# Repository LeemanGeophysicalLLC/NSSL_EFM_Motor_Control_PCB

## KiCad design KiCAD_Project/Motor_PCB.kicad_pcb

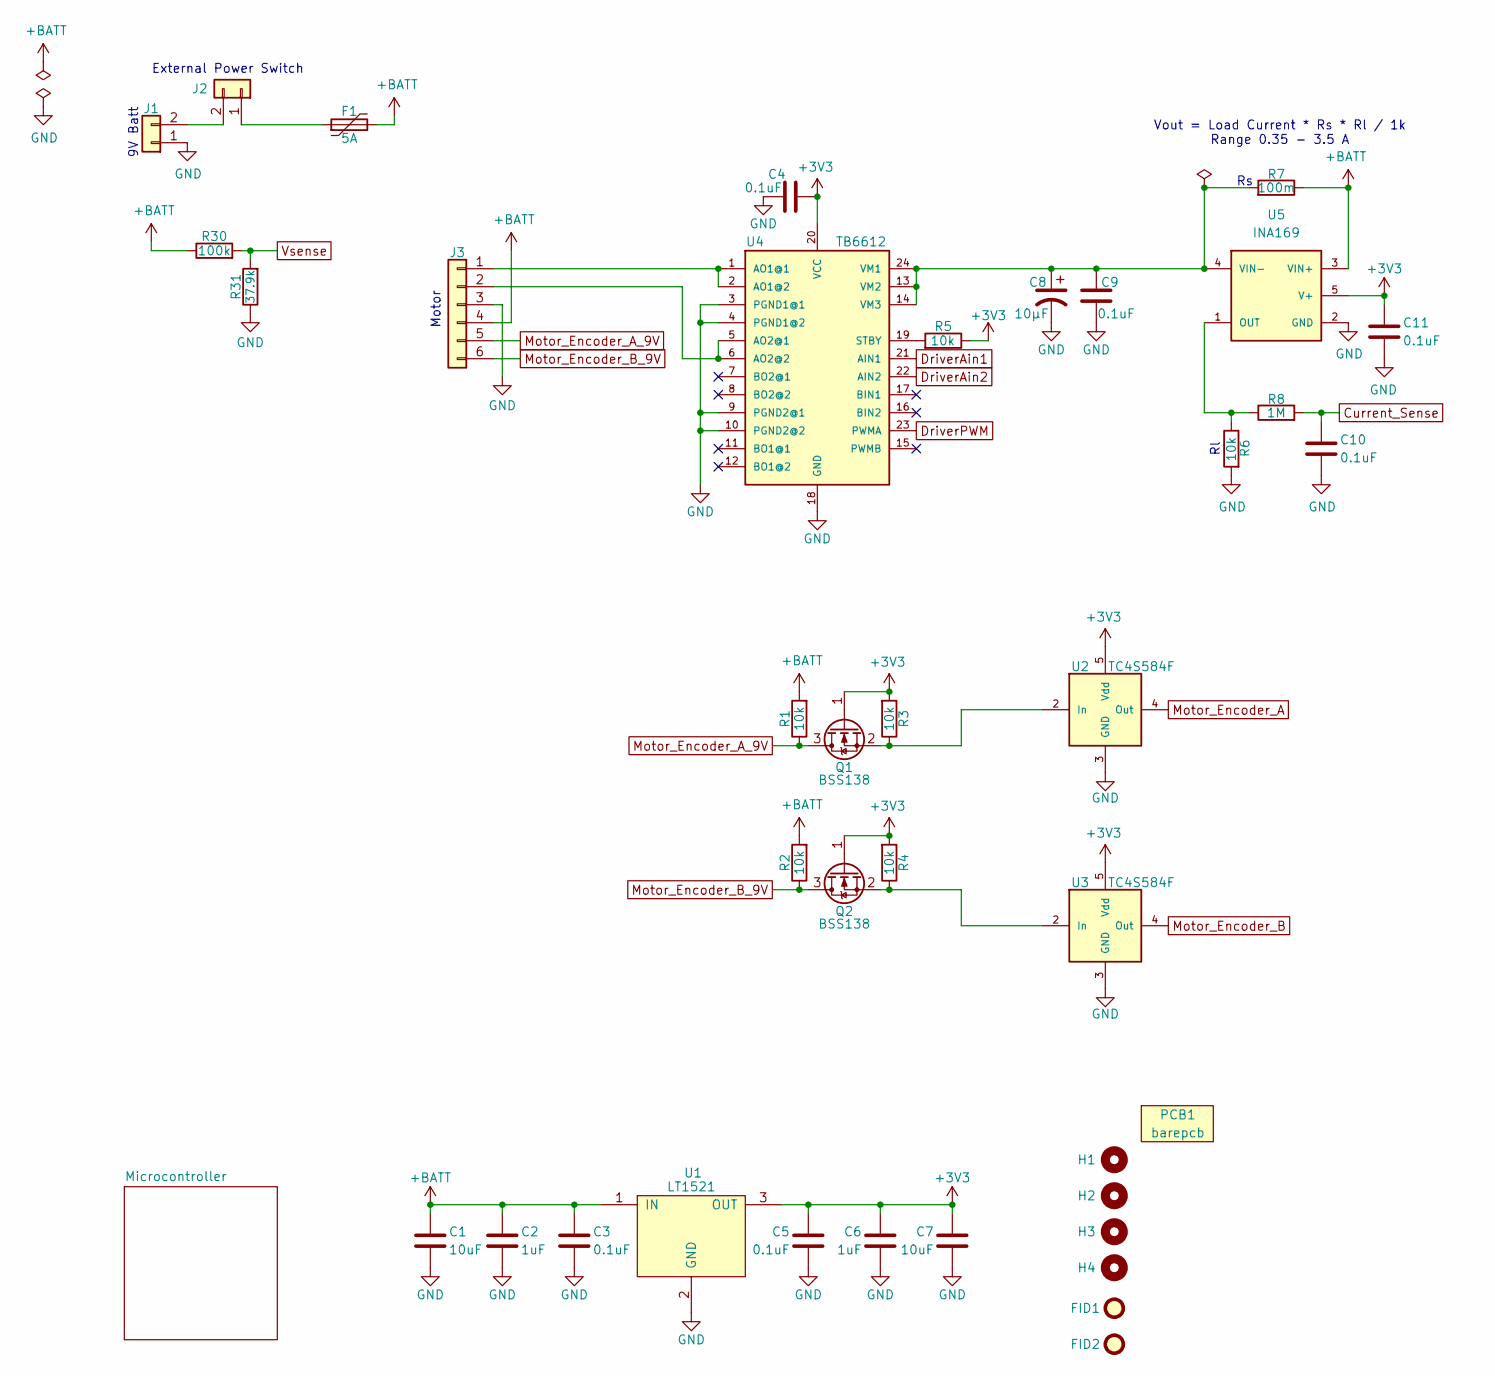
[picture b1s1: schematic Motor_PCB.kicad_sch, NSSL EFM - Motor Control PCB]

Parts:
C1, C7: 1-0000005
C2, C6: 1-0000018
C3, C4, C5, C9, C10, C11: 1-0000007
C8: 1-0000176
F1: 1-0001547
FID1, FID2: Fiducial_1mm_2mm; Fiducial_1mm_Mask2mm
H1, H2, H3, H4: Imperial4; MountingHole_imperial4
J1, J2: NP_Conn_01x02_Relief; SolderWire_1x02_Relief
J3: NP_Conn_01x06; PinHeader_1x06_P2.54mm_Horizontal
PCB1: barepcb
Q1, Q2: 1-0000163
R1, R2, R3, R4, R5, R6: 1-0000010
R7: 1-0001546
R8: 1-0000009
R30: 1-0000174
R31: 1-0001756
U1: 1-0000196
U2, U3: 1-0000456
U4: 1-0001532
U5: 1-0000452

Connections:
+3V3: C4.2, C5.1, C6.1, C7.1, C11.1, Q1.1 (G), Q2.1 (G), R3.2, R4.2, R5.1, U1.3 (OUT), U2.5 (Vdd), U3.5 (Vdd), U4.20 (VCC), U5.5 (V+); also elsewhere on the board
+BATT: C1.1, C2.1, C3.1, F1.2, J3.4, R1.2, R2.2, R7.1, R30.1, U1.1 (IN), U5.3 (VIN+)
Current_Sense: C10.1, R8.2; also elsewhere on the board
DriverAin1: U4.21 (AIN1); also elsewhere on the board
DriverAin2: U4.22 (AIN2); also elsewhere on the board
DriverPWM: U4.23 (PWMA); also elsewhere on the board
GND: C1.2, C2.2, C3.2, C4.1, C5.2, C6.2, C7.2, C8.2, C9.1, C10.2, C11.2, J1.1, J3.3, R6.2, R31.1, U1.2 (GND), U2.3 (GND), U3.3 (GND), U4.3 (PGND1@1), U4.4 (PGND1@2), U4.9 (PGND2@1), U4.10 (PGND2@2), U4.18 (GND), U5.2 (GND); also elsewhere on the board
Motor_Encoder_A: U2.4 (Out); also elsewhere on the board
Motor_Encoder_A_9V: J3.5, Q1.3 (D), R1.1
Motor_Encoder_B: U3.4 (Out); also elsewhere on the board
Motor_Encoder_B_9V: J3.6, Q2.3 (D), R2.1
unnamed: J1.2, J2.2
unnamed: F1.1, J2.1
unnamed: J3.1, U4.1 (AO1@1), U4.2 (AO1@2)
unnamed: J3.2, U4.5 (AO2@1), U4.6 (AO2@2)
unnamed: Q1.2 (S), R3.1, U2.2 (In)
unnamed: Q2.2 (S), R4.1, U3.2 (In)
unnamed: R5.2, U4.19 (STBY)
unnamed: C8.1, C9.2, R7.2, U4.13 (VM2), U4.14 (VM3), U4.24 (VM1), U5.4 (VIN-)
unnamed: R6.1, R8.1, U5.1 (OUT)
Vsense: R30.2, R31.2; also elsewhere on the board

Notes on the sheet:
Motor
External Power Switch
9V Batt
Vout = Load Current * Rs * Rl / 1k Range 0.35 - 3.5 A

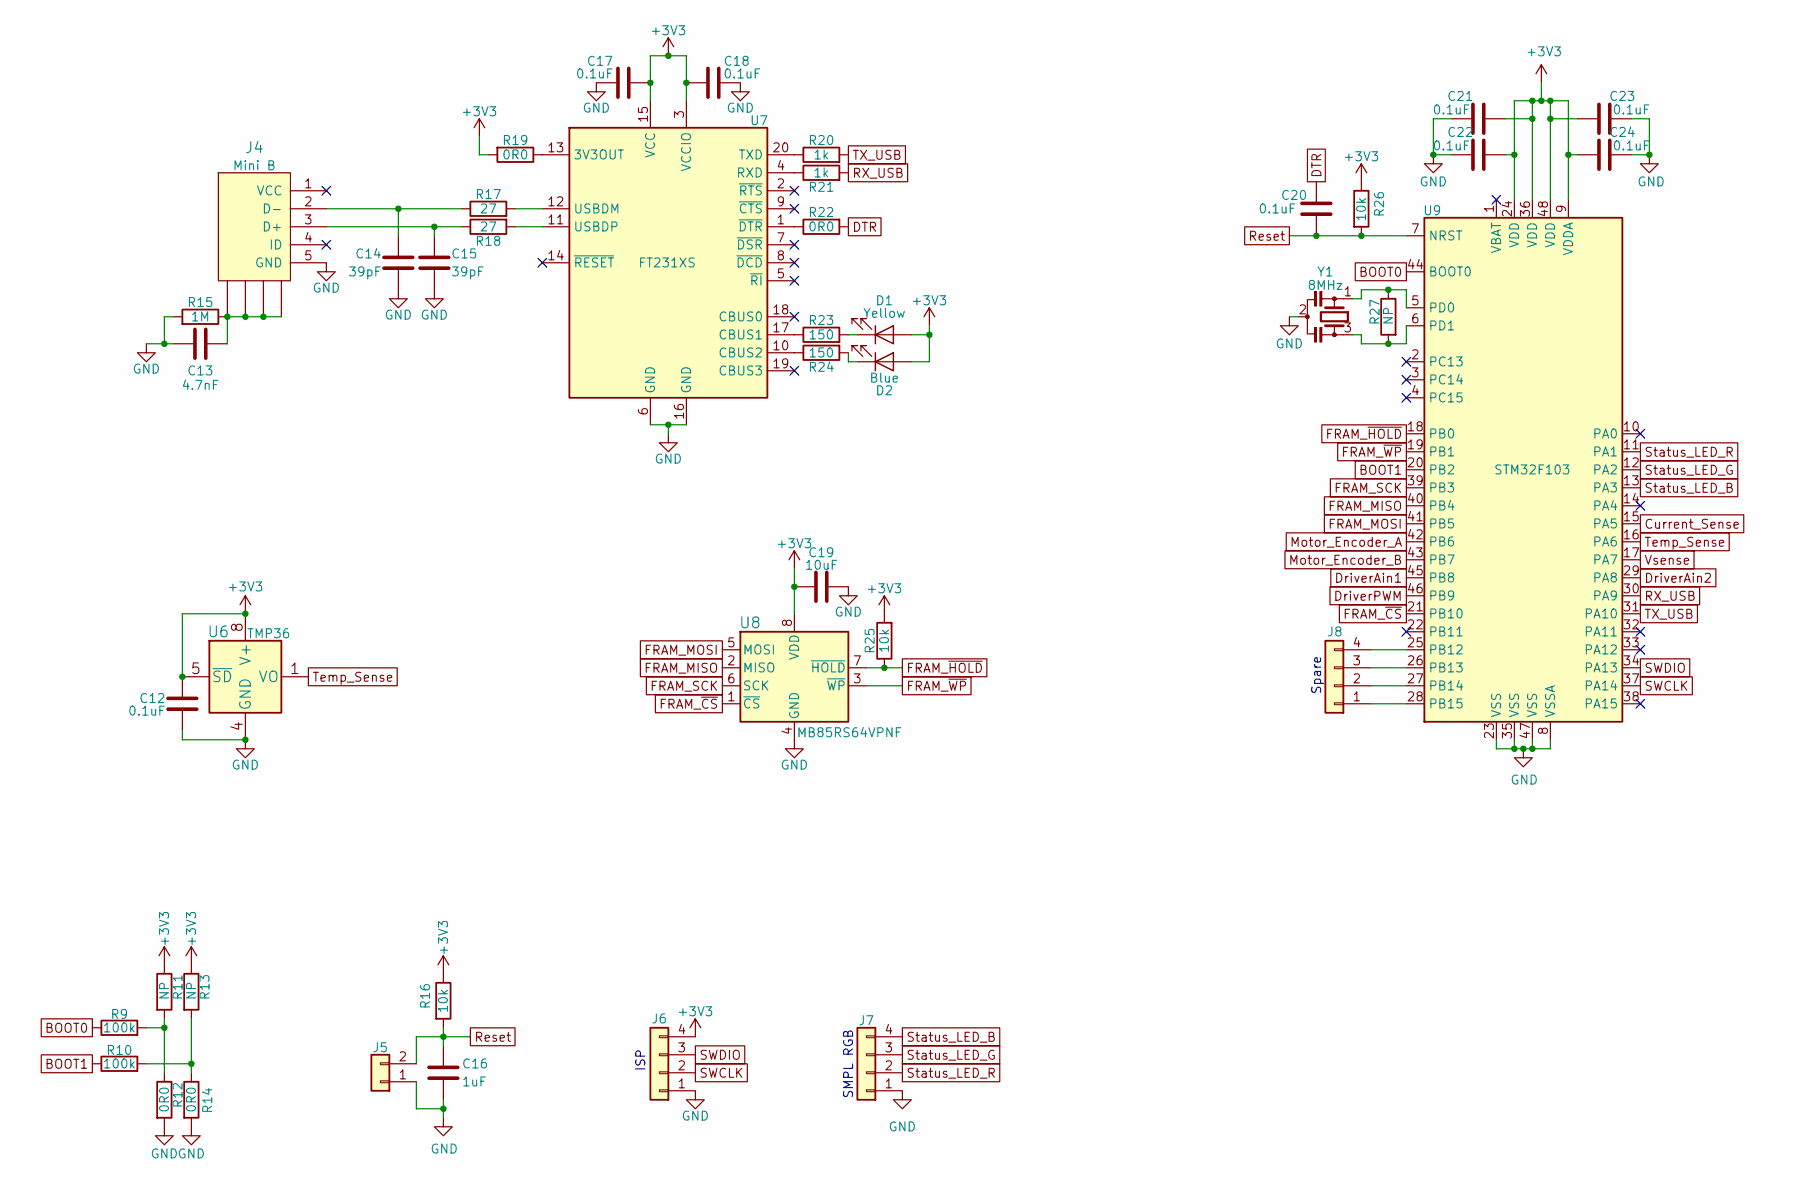
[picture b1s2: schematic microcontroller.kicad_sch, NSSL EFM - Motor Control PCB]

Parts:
C12, C17, C18, C20, C21, C22, C23, C24: 1-0000007
C13: 1-0000016
C14, C15: 1-0000017
C16: 1-0000018
C19: 1-0000005
D1: 1-0000601
D2: 1-0000599
J4: 1-0000034
J5: NP_Conn_01x02; PinHeader_1x02_P2.54mm_Vertical
J6, J8: NP_Conn_01x04; PinHeader_1x04_P2.54mm_Vertical
J7: 1-0001156
R9, R10: 1-0000174
R11, R12, R13, R14, R19, R22, R27: 1-0000006
R15: 1-0000009
R16, R25, R26: 1-0000010
R17, R18: 1-0000012
R20, R21: 1-0000013
R23, R24: 1-0000008
U6: 1-0001493
U7: 1-0000779
U8: 1-0001755
U9: 1-0000207
Y1: 1-0000721

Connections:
+3V3: C12.1, C17.2, C18.2, C19.1, C21.1, C22.1, C23.1, C24.1, D1.2 (A), D2.2 (A), J6.4, R11.1, R13.1, R16.1, R19.2, R25.2, R26.1, U6.5 (~SD), U6.8 (V+), U7.3 (VCCIO), U7.15 (VCC), U8.8 (VDD), U9.9 (VDDA), U9.24 (VDD), U9.36 (VDD), U9.48 (VDD); also elsewhere on the board
BOOT0: R9.1, U9.44 (BOOT0)
BOOT1: R10.1, U9.20 (PB2)
Current_Sense: U9.15 (PA5); also elsewhere on the board
DTR: C20.1, R22.2
DriverAin1: U9.45 (PB8); also elsewhere on the board
DriverAin2: U9.29 (PA8); also elsewhere on the board
DriverPWM: U9.46 (PB9); also elsewhere on the board
FRAM_MISO: U8.2 (MISO), U9.40 (PB4)
FRAM_MOSI: U8.5 (MOSI), U9.41 (PB5)
FRAM_SCK: U8.6 (SCK), U9.39 (PB3)
FRAM_~CS: U8.1 (~CS), U9.21 (PB10)
FRAM_~HOLD: R25.1, U8.7 (~HOLD), U9.18 (PB0)
FRAM_~WP: U8.3 (~WP), U9.19 (PB1)
GND: C12.2, C13.2, C14.2, C15.2, C16.2, C17.1, C18.1, C19.2, C21.2, C22.2, C23.2, C24.2, J4.5 (GND), J5.1, J6.1, J7.1, R12.2, R14.2, R15.2, U6.4 (GND), U7.6 (GND), U7.16 (GND), U8.4 (GND), U9.8 (VSSA), U9.23 (VSS), U9.35 (VSS), U9.47 (VSS), Y1.2; also elsewhere on the board
Motor_Encoder_A: U9.42 (PB6); also elsewhere on the board
Motor_Encoder_B: U9.43 (PB7); also elsewhere on the board
unnamed: C13.1, J4.6 (SHIELD), J4.7 (SHIELD), J4.8 (SHIELD), J4.9 (SHIELD), R15.1
unnamed: D1.1 (K), R23.2
unnamed: D2.1 (K), R24.2
unnamed: C15.1, J4.3 (D+), R18.1
unnamed: C14.1, J4.2 (D-), R17.1
unnamed: J8.1, U9.28 (PB15)
unnamed: J8.2, U9.27 (PB14)
unnamed: J8.3, U9.26 (PB13)
unnamed: J8.4, U9.25 (PB12)
unnamed: R10.2, R13.2, R14.1
unnamed: R9.2, R11.2, R12.1
unnamed: R19.1, U7.13 (3V3OUT)
unnamed: R23.1, U7.17 (CBUS1)
unnamed: R24.1, U7.10 (CBUS2)
unnamed: R21.1, U7.4 (RXD)
unnamed: R20.1, U7.20 (TXD)
unnamed: R17.2, U7.12 (USBDM)
unnamed: R18.2, U7.11 (USBDP)
unnamed: R22.1, U7.1 (~DTR)
unnamed: R27.1, U9.5 (PD0), Y1.1
unnamed: R27.2, U9.6 (PD1), Y1.3
RX_USB: R21.2, U9.30 (PA9)
Reset: C16.1, C20.2, J5.2, R16.2, R26.2, U9.7 (NRST)
SWCLK: J6.2, U9.37 (PA14)
SWDIO: J6.3, U9.34 (PA13)
Status_LED_B: J7.4, U9.13 (PA3)
Status_LED_G: J7.3, U9.12 (PA2)
Status_LED_R: J7.2, U9.11 (PA1)
TX_USB: R20.2, U9.31 (PA10)
Temp_Sense: U6.1 (VO), U9.16 (PA6)
Vsense: U9.17 (PA7); also elsewhere on the board

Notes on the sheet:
ISP
Spare
SMPL RGB

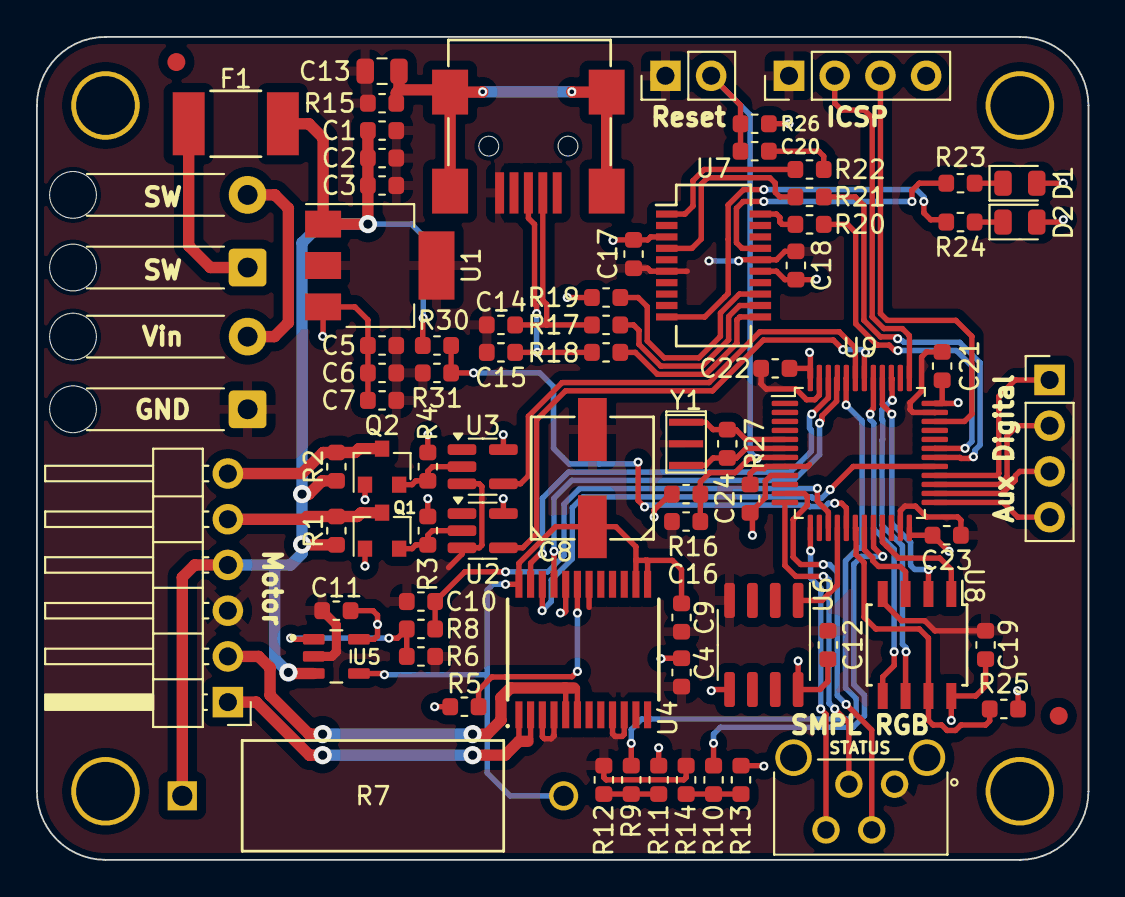
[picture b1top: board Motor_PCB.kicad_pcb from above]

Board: 2 copper layers, 58.4 x 45.7 mm, 83 parts (0 on the bottom side), 60 nets.
